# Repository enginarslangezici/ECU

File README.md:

# ECU v1.0

KiCad ile tasarlanmış 4 katmanlı, 4 enjektör sürücülü, CAN ve Bluetooth destekli motor kontrol ünitesi (ECU) kartı.

> **Durum:** Tasarım tamamlandı (DRC temiz). Kart üretilmedi, proje öğrenme ve portföy amaçlıdır.

**Tasarım:** Engin A. Gezici, 2026

## Özellikler

- 4 kanal enjektör sürücüsü (N-MOSFET + Schottky flyback diyotları)
- 4 kanal ateşleme (IGN) çıkışı (NPN transistör)
- MCP2515 CAN denetleyicisi ve CAN transceiver
- RN42 Bluetooth modülü (kablosuz bağlantı)
- Sensör girişleri: TPS, MAP, CLT, IAT, CRANK, CAM
- 12V akü girişi: TVS diyot ve P-MOSFET ile ters polarite koruması
- L7805 ile 5V, ayrı regülatörle 3.3V
- Programlama/debug başlığı (J1) ve reset/buton (SW1)

## Görseller

## Katman dizilimi

| Katman | Kullanım |
|---|---|
| F.Cu | Bileşenler ve sinyal yolları (SPI, CAN, kristal, UART, gate) |
| In1.Cu | GND düzlemi |
| In2.Cu | 12V_AKU zone'u |
| B.Cu | GND zone'u ve uzun sinyal yolları |

RN42 anten alanında tüm katmanlarda bakır yasak bölgesi vardır.

## Konnektör pin haritası (J17)

| Grup | Pinler |
|---|---|
| Güç | 12V-AKU, GND |
| Enjektör çıkışları | ENJ-1, ENJ-2, ENJ-3, ENJ-4 |
| Ateşleme çıkışları | IGN-1, IGN-2, IGN-3, IGN-4 |
| CAN | CAN-H, CAN-L |
| Sensör girişleri | IN-TPS, IN-MAP, IN-CLT, IN-IAT, IN-CRANK, IN-CAM |

Pin numaralarını ve yönlerini tablo hâlinde eklemek istersen şemaya bakarak genişletebilirsin.

## Ana bileşenler

| Referans | Bileşen | Görev |
|---|---|---|
| U5 | RN42 | Bluetooth |
| U6 | MCP2515 | CAN denetleyici |
| U4 | CAN transceiver | CAN fiziksel katman |
| U1 | L7805 | 5V regülatör |
| U2 | 3.3V regülatör | 3.3V besleme |
| Q1 | P-MOSFET | Ters polarite koruması |
| D1 | TVS | Aşırı gerilim koruması |
| Q2-Q5 | N-MOSFET | Enjektör sürücü |
| Q6-Q9 | NPN | Ateşleme çıkışı |
| Y1 | 8 MHz kristal | MCP2515 saati |
| MCU | STM32F401CCUx 
 | Ana denetleyici |

## Dosyalar

- `KENDİ_ECU.kicad_pro`: proje dosyası
- `KENDİ_ECU.kicad_sch`: şema
- `KENDİ_ECU.kicad_pcb`: kart

KiCad [sürüm numarası] ile açılır.

## Tasarım notları

- 12V dağıtımı kalın izler yerine In2.Cu zone'u ile yapıldı.
- GND için In1.Cu ve B.Cu'da tam düzlem, bileşen GND pedleri via ile bağlanır.
- Kart kenarı pahlı, 3 adet şasi bağlantılı montaj deliği var.

## Yapılacaklar

- [ ] 12V girişe sigorta
- [ ] Güç LED'i
- [ ] Test noktaları
- [ ] Sensör girişlerine TVS/Zener koruma
- [ ] MOSFET gate Zener'leri
- [ ] CAN terminasyon jumper'ı

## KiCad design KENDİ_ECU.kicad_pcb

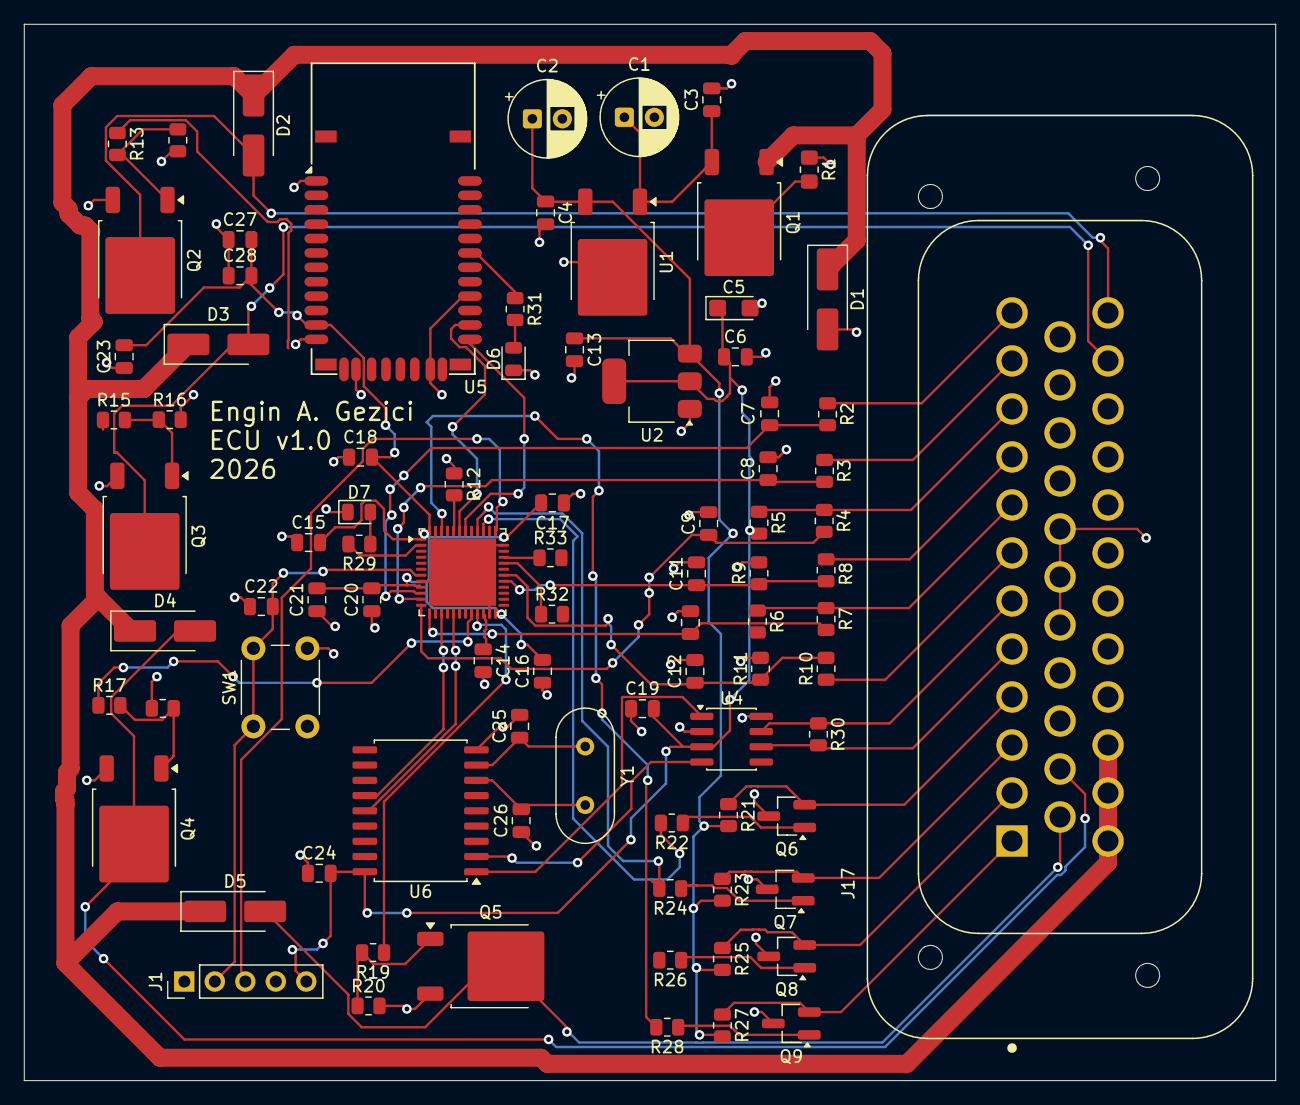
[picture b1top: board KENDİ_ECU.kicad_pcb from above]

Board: 2 copper layers, 104.3 x 88.0 mm, 87 parts (0 on the bottom side), 65 nets.

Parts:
C1, C2: 22uF; CP_Radial_D6.3mm_P2.50mm
C3: 330nF; C_0805_2012Metric
C4, C6, C7, C8, C9, C10, C13, C15, C16, C17, C18, C21, C22, C23, C24, C28: 100nF; C_0805_2012Metric
C5: 22uF; CP_EIA-3216-18_Kemet-A
C11, C12: 1nF; C_0805_2012Metric
C14: 2.2uF; C_0805_2012Metric
C19: 4.7uF; C_0805_2012Metric
C20: 1uF; C_0805_2012Metric
C25, C26: 22pF; C_0805_2012Metric
C27: 10uF; C_0805_2012Metric
D1: D_TVS; D_SMA_Handsoldering
D2, D3, D4, D5: D_Schottky; D_SMA_Handsoldering
D6, D7: LED; LED_0805_2012Metric
J1: Conn_01x05; PinHeader_1x05_P2.54mm_Vertical
J17: 776231-1; TE_776231-1
Q1: Q_PMOS_DGS; TO-252-2
Q2, Q3, Q4, Q5: Q_NMOS_GDS; TO-252-2
Q6, Q7, Q8, Q9: Q_NPN_BCE; SOT-23_Handsoldering
R1: 10K; R_0805_2012Metric_Pad1.20x1.40mm_HandSolder
R2, R3, R4, R7, R29, R31: 1K; R_0805_2012Metric
R5, R6, R8, R10: 2.2K; R_0805_2012Metric
R9, R11: 3.3k; R_0805_2012Metric
R12, R14, R16, R18, R20, R32, R33: 10K; R_0805_2012Metric
R13, R15, R17, R19: 330Ω; R_0805_2012Metric
R21, R22, R23, R24, R25, R26, R27, R28: 1kΩ; R_0805_2012Metric
R30: 120Ω; R_0805_2012Metric
SW1: SW_Push; SW_PUSH_6mm
U1: L7805; TO-252-2
U2: AMS1117-3.3; SOT-223-3_TabPin2
U3: STM32F401CCUx; QFN-48-1EP_7x7mm_P0.5mm_EP5.6x5.6mm
U4: SN65HVD230; SOIC-8_3.9x4.9mm_P1.27mm
U5: RN42
U6: MCP2515-xSO; SOIC-18W_7.5x11.6mm_P1.27mm
Y1: 8MHz; Crystal_HC49-4H_Vertical

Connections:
12V_AKU: D1.1 (A1), D2.1 (K), D3.1 (K), D4.1 (K), D5.1 (K), J17.24, J17.25, J17.26, Q1.1 (D)
+3V3: C5.1, C6.1, C15.2, C16.2, C17.2, C18.2, C19.2, C20.2, C21.2, C23.2, C24.2, C27.2, C28.2, J1.5, R5.2, R6.2, R32.2, R33.2, U2.2 (VO), U3.1 (VBAT), U3.9 (VREF+), U3.24 (VDD), U3.36 (VDD), U3.48 (VDD), U4.3 (VCC), U5.11 (VDD), U6.18 (VDD)
+5V: C2.1, C4.1, C13.1, R21.2, R23.2, R25.2, R27.2, U1.3 (OUT), U2.3 (VI)
BT_RX: U3.42 (PB6), U5.13 (UART_RX)
BT_TX: U3.43 (PB7), U5.14 (UART_TX)
CAM_DIGITAL: C12.1, R10.2, R11.1, U3.30 (PA9)
CAN_CS: U3.14 (PA4), U6.16 (~CS)
CAN_H: J17.6, R30.1, U4.7 (CANH)
CAN_INT: R32.1, U3.32 (PA11), U6.12 (~INT)
CAN_L: J17.5, R30.2, U4.6 (CANL)
CAN_RESET: R33.1, U3.33 (PA12), U6.17 (~RESET)
CAN_RX: U4.4 (R), U6.2 (RXCAN)
CAN_TX: U4.1 (D), U6.1 (TXCAN)
CLT_ADC: C9.1, R4.2, U3.12 (PA2)
CRANK_DIGITAL: C11.1, R8.2, R9.1, U3.29 (PA8)
ENJ_1: D2.2 (A), J17.35, Q2.2 (D)
ENJ_2: D3.2 (A), J17.34, Q3.2 (D)
ENJ_3: D4.2 (A), J17.14, Q4.2 (D)
ENJ_4: D5.2 (A), J17.13, Q5.2 (D)
GND: C1.2, C2.2, C3.2, C4.2, C5.2, C6.2, C7.2, C8.2, C9.2, C10.2, C11.2, C12.2, C13.2, C14.2, C15.1, C16.1, C17.1, C18.1, C19.1, C20.1, C21.1, C22.1, C23.1, C24.1, C25.2, C26.1, C27.1, C28.1, D1.2 (A2), D6.1 (K), D7.1 (K), J1.1, J17.17, J17.18, J17.19, Q2.3 (S), Q3.3 (S), Q4.3 (S), Q5.3 (S), Q6.3 (E), Q7.3 (E), Q8.3 (E), Q9.3 (E), R1.1, R9.2, R11.2, R12.1, R14.2, R16.2, R18.2, R20.2, SW1.2, U1.2 (GND), U2.1 (GND), U3.8 (VSSA), U3.23 (VSS), U3.35 (VSS), U3.47 (VSS), U3.49 (VSS), U4.2 (GND), U4.8 (Rs), U5.1 (GND), U5.12 (GND), U5.16 (UART_CTS), U5.28 (GND), U5.29 (GND), U6.9 (VSS)
IAT_ADC: C10.1, R7.2, U3.13 (PA3)
IGN1_CTRL: R22.2, U3.39 (PB3)
IGN2_CTRL: R24.2, U3.40 (PB4)
IGN3_CTRL: R26.2, U3.41 (PB5)
IGN4_CTRL: R28.2, U3.46 (PB9)
IGN_1: J17.4, Q6.2 (C), R21.1
IGN_2: J17.3, Q7.2 (C), R23.1
IGN_3: J17.2, Q8.2 (C), R25.1
IGN_4: J17.1, Q9.2 (C), R27.1
INJ1_CTRL: R13.1, U3.18 (PB0)
INJ2_CTRL: R15.1, U3.19 (PB1)
INJ3_CTRL: R17.1, U3.20 (PB2)
INJ4_CTRL: R19.1, U3.21 (PB10)
IN_CAM: J17.7, R10.1
IN_CLT: J17.10, R4.1, R5.1
IN_CRANK: J17.9, R8.1
IN_IAT: J17.8, R6.1, R7.1
IN_MAP: J17.11, R3.1
IN_TPS: J17.12, R2.1
MAP_ADC: C8.1, R3.2, U3.11 (PA1)
NRST: C22.2, J1.2, SW1.1, U3.7 (NRST)
unnamed: D6.2 (A), R31.2
unnamed: D7.2 (A), R29.1
unnamed: Q1.2 (G), R1.2
unnamed: C1.1, C3.1, Q1.3 (S), U1.1 (IN)
unnamed: Q2.1 (G), R13.2, R14.1
unnamed: Q3.1 (G), R15.2, R16.1
unnamed: Q4.1 (G), R17.2, R18.1
unnamed: Q5.1 (G), R19.2, R20.1
unnamed: Q6.1 (B), R22.1
unnamed: Q7.1 (B), R24.1
unnamed: Q8.1 (B), R26.1
unnamed: Q9.1 (B), R28.1
unnamed: R12.2, U3.44 (BOOT0)
unnamed: R29.2, U3.2 (PC13)
unnamed: C14.1, U3.22 (VCAP1)
unnamed: R31.1, U5.19 (GPIO2)
unnamed: C25.1, U6.8 (OSC1), Y1.1
unnamed: C26.2, U6.7 (OSC2), Y1.2
SPI1_MISO: U3.16 (PA6), U6.15 (SO)
SPI1_MOSI: U3.17 (PA7), U6.14 (SI)
SPI1_SCK: U3.15 (PA5), U6.13 (SCK)
SWCLK: J1.3, U3.37 (PA14)
SWDIO: J1.4, U3.34 (PA13)
TPS_ADC: C7.1, R2.2, U3.10 (PA0)
